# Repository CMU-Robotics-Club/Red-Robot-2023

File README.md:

# Red-Robot-2023
A repository for all of the resouces for the 2023 Red Robot Hackathon.

## Software Setup

### Arduino IDE & Code Setup

1. Install [The Arduino IDE](https://www.arduino.cc/en/software).
2. Install [support for the Pi Pico](https://github.com/earlephilhower/arduino-pico#installation).
3. Download the repository and unzip it to a convenient place on your computer.
4. Open `Arduino-Starter.ino`
5. Select the Raspberry Pi Pico (NOT Pico W and NOT the Mbed version) in the dropdown on the top left. You may need to plug in the Pico first.
6. Once you have selected the Pico, go to the library manager, and search for and install "RF24".

### Controller Setup

#### Windows

Install [Python 3](https://www.python.org/downloads/) from the official website.

You will also need to install [drivers for the radio module](https://www.wch-ic.com/downloads/CH341SER_ZIP.html).

#### Mac

Install [Python 3](https://www.python.org/downloads/) from the official website.

The drivers for the radio module should be installed by default.

#### Linux (Ubuntu / Debian) 

Install Python 3, probably using a command like the following:

```
$ sudo apt install python3
```

If you're on Linux, you may need to uninstall the Braille TTY to make the radio work properly.

```
$ sudo apt remove brltty
```

Then, you will need to add your user to the dialout group to use the radio.

```
$ sudo useradd yourusernamehere dialout
```

Log out and log in again to make the group change take effect.

## Programming the Radio
Before you can control your robot you will need to program your radio. Plug
the radio into the adapter board like this:

Run either `program_radio_mac.sh` or `program_radio_windows.sh`, depending on
your operating system. This will prompt for your team number (this is the
number on the side of your kit)

## Deploying Code

Steps 1-3 may not be necessary depending on your computer.
If the Arduino IDE tells you it can't find the Pico, try doing them.

1. Unplug the Pico from battery power and from the USB port.
  (It may be easiser to unplug the USB cable from your computer, as the Pico's USB port can be stiff).
2. Hold down the small button on the Pico.
3. While still holding down the button, plug the USB port back in.
4. Press the "Upload" button (arrow) in the top left corner.

The Arduino IDE's serial monitor can be somewhat unreliable,
so if you'd like to see output from your Pico,
you should probably [install CoolTerm](https://freeware.the-meiers.org).
Once in CoolTerm, simply select the Pico in the bottom left and set the Baud Rate to 115200, then click "connect."
Be careful not to accidentally select the radio module instead.

## Controlling The Robot

1. Flip the controller over and make sure the switch on the back is set to "D".
2. Plug the controller into your computer.
3. Plug the radio module into your computer.
5. Depending on your operating system, open `run_mac.sh` or `run_windows.bat`.

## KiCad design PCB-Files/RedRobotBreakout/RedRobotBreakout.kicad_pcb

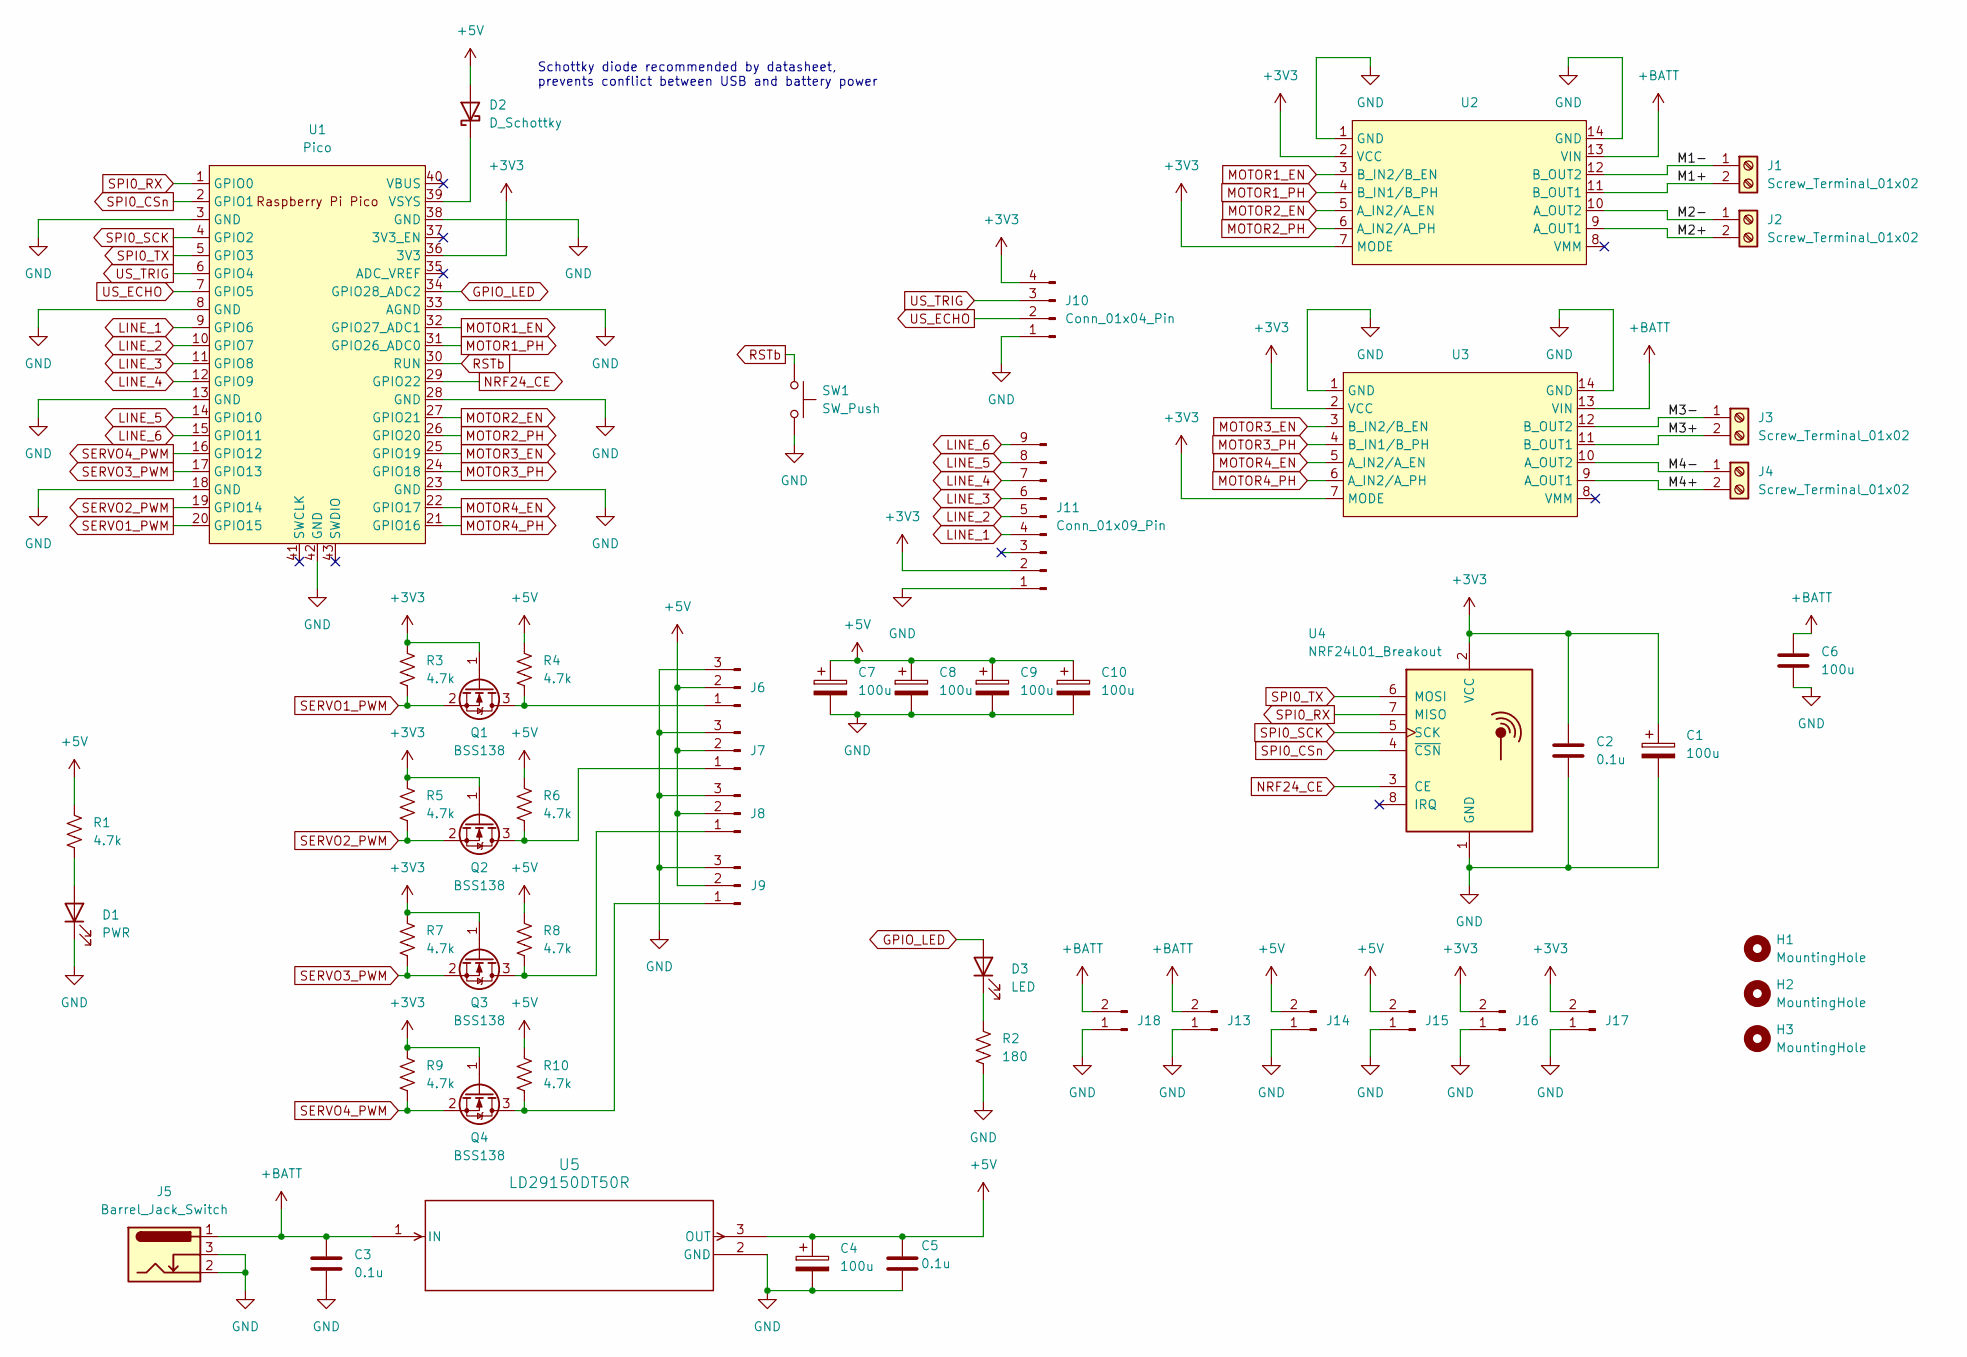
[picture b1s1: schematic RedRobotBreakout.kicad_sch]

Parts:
C1, C4, C6, C7, C8, C9, C10: 100u; CP_Elec_5x5.4; JLC P/N C22387981
C2, C3, C5: 0.1u; C_1206_3216Metric_Pad1.33x1.80mm_HandSolder; JLC P/N C24497
D1: PWR; LED_0805_2012Metric_Pad1.15x1.40mm_HandSolder; JLC P/N C2297
D2: D_Schottky; SOT-23; JLC P/N C22466368
D3: LED; LED_0603_1608Metric_Pad1.05x0.95mm_HandSolder; JLC P/N C2286
H1, H2, H3: MountingHole; MountingHole_3.2mm_M3_Pad_Via
J1, J2, J3, J4: Screw_Terminal_01x02; ScrewTerminalP3.5mm; JLC P/N C695629
J5: Barrel_Jack_Switch; BarrelJack_Horizontal; JLC P/N C136744
J6, J7, J8, J9: Conn_01x03_Pin; PinHeader_1x03_P2.54mm_Vertical; JLC P/N C6332196
J10: Conn_01x04_Pin; PinHeader_1x04_P2.54mm_Vertical; JLC P/N C6332197
J11: Conn_01x09_Pin; PinHeader_1x09_P2.54mm_Vertical; JLC P/N C492408
J13, J14, J15, J16, J17, J18: Conn_01x02_Pin; PinHeader_1x02_P2.54mm_Vertical; JLC P/N C2905434
Q1, Q2, Q3, Q4: BSS138; SOT-23; JLC P/N C112239
R1, R3, R4, R5, R6, R7, R8, R9, R10: 4.7k; R_1206_3216Metric_Pad1.30x1.75mm_HandSolder; JLC P/N C17936
R2: 180; R_1206_3216Metric_Pad1.30x1.75mm_HandSolder; JLC P/N C17924
SW1: SW_Push; SW_Push_1P1T_XKB_TS-1187A; JLC P/N C318884
U1: Pico; RPi_Pico_SMD_TH
U2, U3: DRV8835
U4: NRF24L01_Breakout; nRF24L01_Breakout; JLC P/N C92271
U5: LD29150DT50R; TO-252-2; JLC P/N C157411

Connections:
+3V3: C1.1, C2.1, J10.4, J11.2, J16.2, J17.2, Q1.1 (G), Q2.1 (G), Q3.1 (G), Q4.1 (G), R3.1, R5.1, R7.1, R9.1, U1.36 (3V3), U2.2 (VCC), U2.7 (MODE), U3.2 (VCC), U3.7 (MODE), U4.2 (VCC)
+5V: C4.1, C5.1, C7.1, C8.1, C9.1, C10.1, D2.2 (A), J6.2, J7.2, J8.2, J9.2, J14.2, J15.2, R1.1, R4.1, R6.1, R8.1, R10.1, U5.3 (OUT)
+BATT: C3.1, C6.1, J5.1, J13.2, J18.2, U2.13 (VIN), U3.13 (VIN), U5.1 (IN)
/M1+: J1.2, U2.11 (B_OUT1)
/M1-: J1.1, U2.12 (B_OUT2)
/M2+: J2.2, U2.9 (A_OUT1)
/M2-: J2.1, U2.10 (A_OUT2)
/M3+: J3.2, U3.11 (B_OUT1)
/M3-: J3.1, U3.12 (B_OUT2)
/M4+: J4.2, U3.9 (A_OUT1)
/M4-: J4.1, U3.10 (A_OUT2)
GND: C1.2, C2.2, C3.2, C4.2, C5.2, C6.2, C7.2, C8.2, C9.2, C10.2, D1.1 (K), J5.2, J5.3, J6.3, J7.3, J8.3, J9.3, J10.1, J11.1, J13.1, J14.1, J15.1, J16.1, J17.1, J18.1, R2.2, SW1.2, U1.3 (GND), U1.8 (GND), U1.13 (GND), U1.18 (GND), U1.23 (GND), U1.28 (GND), U1.33 (AGND), U1.38 (GND), U1.42 (GND), U2.1 (GND), U2.14 (GND), U3.1 (GND), U3.14 (GND), U4.1 (GND), U5.2 (GND)
GPIO_LED: D3.2 (A), U1.34 (GPIO28_ADC2)
LINE_1: J11.4, U1.9 (GPIO6)
LINE_2: J11.5, U1.10 (GPIO7)
LINE_3: J11.6, U1.11 (GPIO8)
LINE_4: J11.7, U1.12 (GPIO9)
LINE_5: J11.8, U1.14 (GPIO10)
LINE_6: J11.9, U1.15 (GPIO11)
MOTOR1_EN: U1.32 (GPIO27_ADC1), U2.3 (B_IN2/B_EN)
MOTOR1_PH: U1.31 (GPIO26_ADC0), U2.4 (B_IN1/B_PH)
MOTOR2_EN: U1.27 (GPIO21), U2.5 (A_IN2/A_EN)
MOTOR2_PH: U1.26 (GPIO20), U2.6 (A_IN2/A_PH)
MOTOR3_EN: U1.25 (GPIO19), U3.3 (B_IN2/B_EN)
MOTOR3_PH: U1.24 (GPIO18), U3.4 (B_IN1/B_PH)
MOTOR4_EN: U1.22 (GPIO17), U3.5 (A_IN2/A_EN)
MOTOR4_PH: U1.21 (GPIO16), U3.6 (A_IN2/A_PH)
NRF24_CE: U1.29 (GPIO22), U4.3 (CE)
unnamed: D1.2 (A), R1.2
unnamed: D2.1 (K), U1.39 (VSYS)
unnamed: D3.1 (K), R2.1
unnamed: J6.1, Q1.3 (D), R4.2
unnamed: J7.1, Q2.3 (D), R6.2
unnamed: J8.1, Q3.3 (D), R8.2
unnamed: J9.1, Q4.3 (D), R10.2
RSTb: SW1.1, U1.30 (RUN)
SERVO1_PWM: Q1.2 (S), R3.2, U1.20 (GPIO15)
SERVO2_PWM: Q2.2 (S), R5.2, U1.19 (GPIO14)
SERVO3_PWM: Q3.2 (S), R7.2, U1.17 (GPIO13)
SERVO4_PWM: Q4.2 (S), R9.2, U1.16 (GPIO12)
SPI0_CSn: U1.2 (GPIO1), U4.4 (~CSN)
SPI0_RX: U1.1 (GPIO0), U4.7 (MISO)
SPI0_SCK: U1.4 (GPIO2), U4.5 (SCK)
SPI0_TX: U1.5 (GPIO3), U4.6 (MOSI)
US_ECHO: J10.2, U1.7 (GPIO5)
US_TRIG: J10.3, U1.6 (GPIO4)

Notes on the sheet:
Schottky diode recommended by datasheet, prevents conflict between USB and battery power

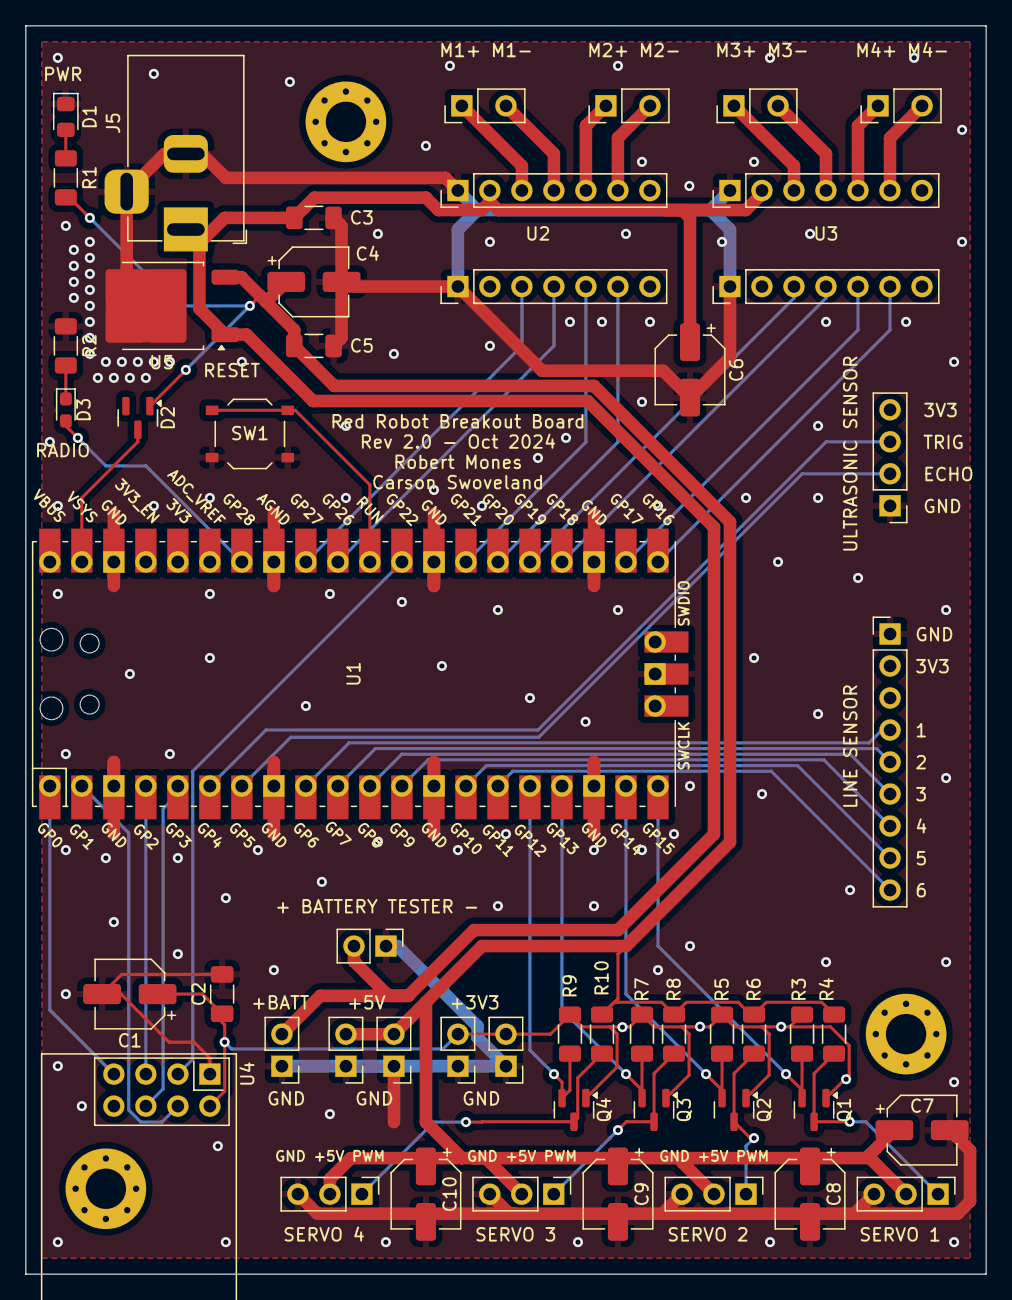
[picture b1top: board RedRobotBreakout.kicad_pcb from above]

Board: 4 copper layers, 76.2 x 99.1 mm, 53 parts (0 on the bottom side), 46 nets.

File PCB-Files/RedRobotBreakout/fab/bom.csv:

"Reference","Value","Footprint","Description","JLC P/N"
"C1,C4,C6,C7,C8,C9,C10","100u","Capacitor_SMD:CP_Elec_5x5.4","","C22387981"
"C2,C3,C5","0.1u","Capacitor_SMD:C_1206_3216Metric_Pad1.33x1.80mm_HandSolder","","C24497"
"D1","PWR","LED_SMD:LED_0805_2012Metric_Pad1.15x1.40mm_HandSolder","","C2297"
"D2","D_Schottky","Package_TO_SOT_SMD:SOT-23","","C22466368"
"D3","LED","LED_SMD:LED_0603_1608Metric_Pad1.05x0.95mm_HandSolder","Light emitting diode","C2286"
"H1,H2,H3","MountingHole","MountingHole:MountingHole_3.2mm_M3_Pad_Via","",""
"J1,J2,J3,J4","Screw_Terminal_01x02","RedRobotFootprints:ScrewTerminalP3.5mm","","C5349543"
"J5","Barrel_Jack_Switch","Connector_BarrelJack:BarrelJack_Horizontal","","C136744"
"J6,J7,J8,J9","Conn_01x03_Pin","Connector_PinHeader_2.54mm:PinHeader_1x03_P2.54mm_Vertical","","C6332196"
"J10","Conn_01x04_Pin","Connector_PinHeader_2.54mm:PinHeader_1x04_P2.54mm_Vertical","","C6332197"
"J11","Conn_01x09_Pin","Connector_PinHeader_2.54mm:PinHeader_1x09_P2.54mm_Vertical","","C492408"
"J13,J14,J15,J16,J17,J18","Conn_01x02_Pin","Connector_PinHeader_2.54mm:PinHeader_1x02_P2.54mm_Vertical","","C2905434"
"Q1,Q2,Q3,Q4","BSS138","Package_TO_SOT_SMD:SOT-23","50V Vds, 0.22A Id, N-Channel MOSFET, SOT-23","C112239"
"R1,R3,R4,R5,R6,R7,R8,R9,R10","4.7k","Resistor_SMD:R_1206_3216Metric_Pad1.30x1.75mm_HandSolder","","C17936"
"R2","180","Resistor_SMD:R_1206_3216Metric_Pad1.30x1.75mm_HandSolder","","C17924"
"SW1","SW_Push","Button_Switch_SMD:SW_Push_1P1T_XKB_TS-1187A","Push button switch, generic, two pins","C318884"
"U1","Pico","MCU_RaspberryPi_and_Boards:RPi_Pico_SMD_TH","",""
"U2,U3","~","RedRobotFootprints:DRV8835","",""
"U4","NRF24L01_Breakout","RF_Module:nRF24L01_Breakout","","C92271"
"U5","HT7805ARMZ","Package_TO_SOT_SMD:TO-252-2","","C5336215"

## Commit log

2023-11-04 Updated run scripts
2023-11-04 Modify run script to use pygame instead
2024-11-01 Updated for 2024
2024-11-01 Fixed Update for 2024
    This reverts part of commit b41f08040d1129fef7a20f06438e1e1cbf41e864.
2024-11-01 Increased controller broadcast rate
2024-11-02 Fixed missing recv_first_packet
2025-08-05 added PCB files from 2024, have not been edited yet
2025-08-20 removed duplicate pcb files
2025-11-01 Fixed number of teams
2025-11-01 Changed scaling factor
2025-11-01 Updated team number comments
2025-11-06 nRF dongle program script
2025-11-07 radio program instructions + rename
